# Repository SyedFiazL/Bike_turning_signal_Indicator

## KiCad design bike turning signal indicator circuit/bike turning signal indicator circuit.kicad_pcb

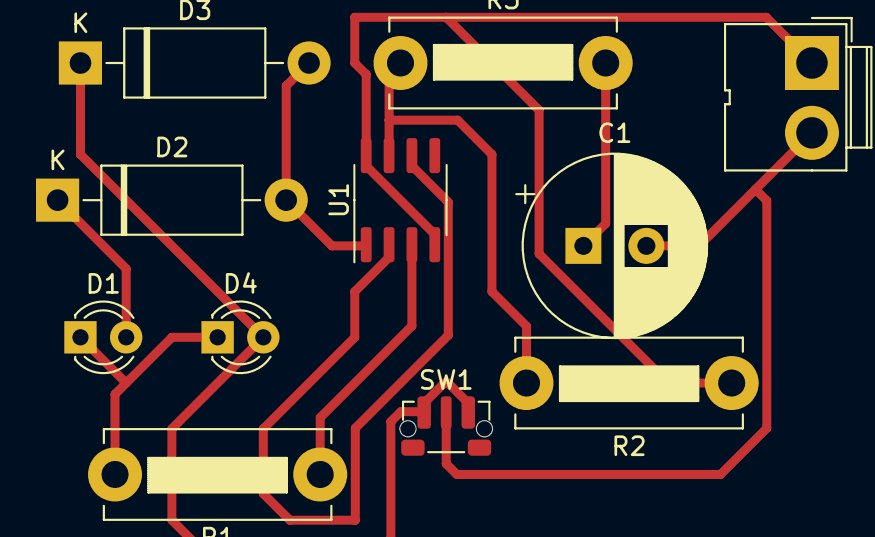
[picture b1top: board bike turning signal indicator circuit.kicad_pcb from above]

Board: 2 copper layers, 11 parts (0 on the bottom side), 10 nets.

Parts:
B1: Conn_01x02; JWT_A3963_1x02_P3.96mm_Vertical
C1: 1uF; CP_Radial_D10.0mm_P3.50mm
D1, D4: LED; LED_D3.0mm
D2, D3: 1N4007; D_DO-15_P12.70mm_Horizontal
R1: 180; R_Bare_Metal_Element_L12.4mm_W4.8mm_P11.40mm
R2: 100k; R_Bare_Metal_Element_L12.4mm_W4.8mm_P11.40mm
R3: 470k; R_Bare_Metal_Element_L12.4mm_W4.8mm_P11.40mm
SW1: SW_SPDT; SW_Push_1P1T-MP_NO_Horizontal_Alps_SKRTLAE010
U1: LM555xM; SOIC-8_3.9x4.9mm_P1.27mm

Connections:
unnamed: B1.1, R2.1, U1.4 (R), U1.8 (VCC)
unnamed: B1.2, C1.2, SW1.2 (B)
unnamed: C1.1, R3.2
unnamed: D1.1 (K), D4.1 (K), R1.2
unnamed: D1.2 (A), D2.1 (K)
unnamed: D2.2 (A), D3.2 (A), U1.1 (GND)
unnamed: D3.1 (K), D4.2 (A), SW1.1 (A)
unnamed: R1.1, U1.3 (Q)
unnamed: R2.2, R3.1, U1.7 (DIS)
unnamed: U1.2 (TR), U1.6 (THR)
